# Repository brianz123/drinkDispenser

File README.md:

# Drink Dispenser

The Drink Dispenser is an Arduino-powered project designed to automatically fill one to six cups with the drink of your choice. Built as a personal engineering challenge, this project combines hardware control, PCB design, and 3D modeling to create a functional and customizable beverage distribution system.

## Summary

This project was built for fun to explore hardware control, fluid management, and embedded systems. It uses an Arduino to control a water pump and distributes fluid into up to six glasses based on user input selected with a rotary encoder. LEDs connected to an I/O expander provide visual feedback on the number of drinks selected. The mechanical frame was designed in Autodesk Inventor, and the control board was custom-designed in KiCad.

## Features

- Dispenses to 1–6 cups automatically
- Rotary encoder for selecting number of drinks
- LED display (via I/O expander) to show selection in real time
- Arduino-based pump control system
- 3D-modeled and printed parts using Autodesk Inventor
- Custom PCB designed in KiCad
- Modular design for future upgrades

## Hardware

- Arduino microcontroller
- Water pump
- Tubing and splitter manifold
- Rotary encoder
- LEDs + I/O expander (for display)
- 3D-printed frame and mounts (modeled in Inventor)
- Custom PCB (designed in KiCad)

## Software

- Arduino IDE for microcontroller programming
- Rotary encoder logic to select drink quantity
- I/O expander control for LED output
- Time-controlled activation of water pump
- Open-source and adaptable for other types of liquids or expanded glass counts

## Project Goals

- Practice PCB design using KiCad
- Integrate mechanical design with embedded electronics
- Implement real-time user input and feedback system
- Build a fully functional end-to-end automated system

## Future Improvements

- Add touchscreen interface or Bluetooth app control
- Integrate flow sensors for volume precision
- Add cleaning cycle logic for tubing
- Expand I/O expander usage for more LEDs or feedback signals

## Author

**Brian Zagalsky**

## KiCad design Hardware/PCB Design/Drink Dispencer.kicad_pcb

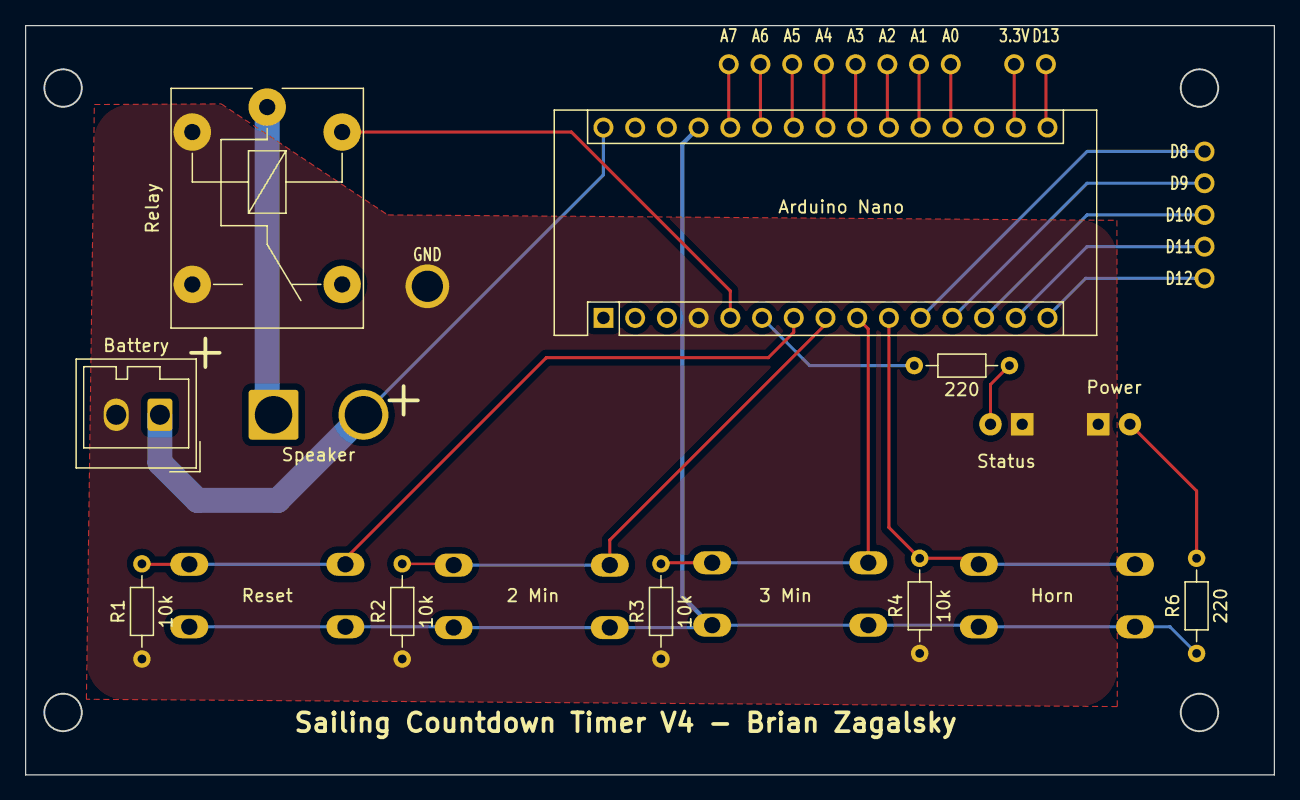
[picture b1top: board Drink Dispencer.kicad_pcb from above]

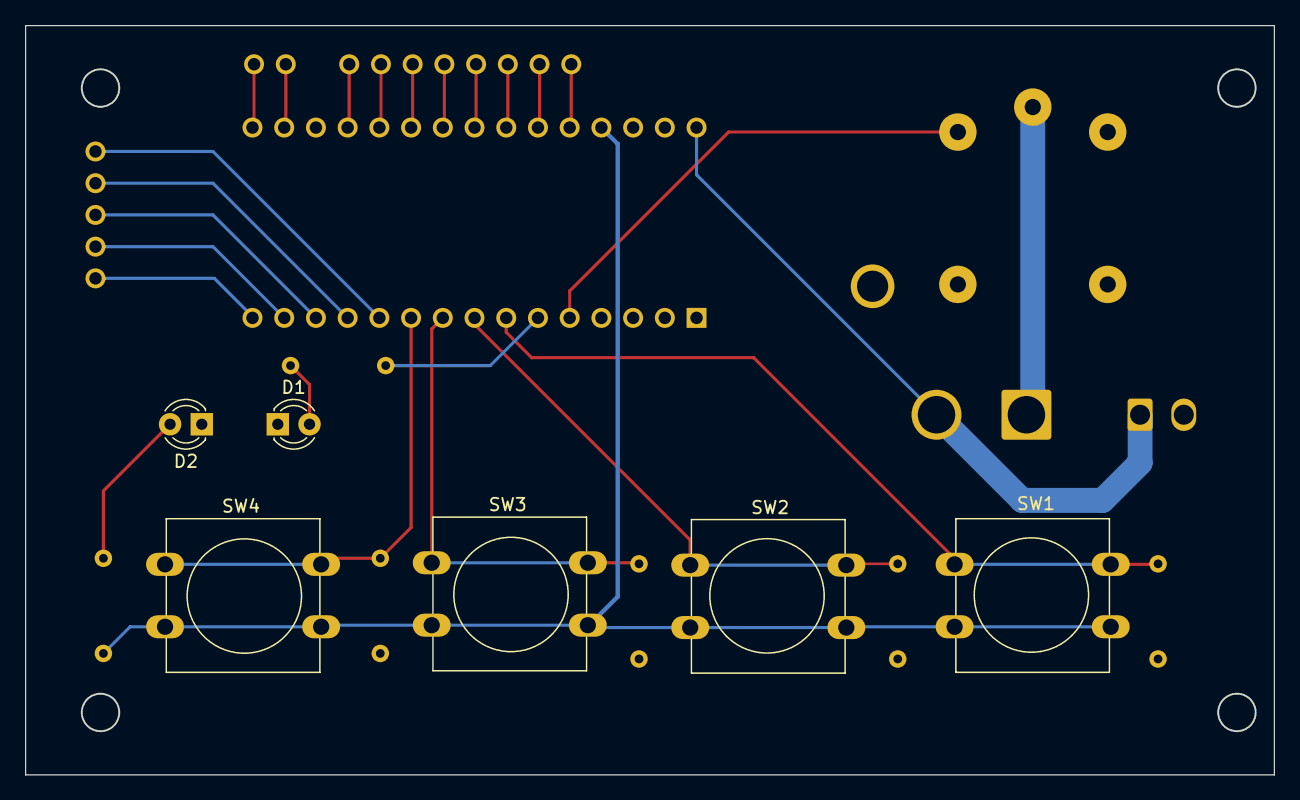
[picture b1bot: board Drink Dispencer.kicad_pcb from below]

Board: 2 copper layers, 100.0 x 59.9 mm, 32 parts (6 on the bottom side), 12 nets.

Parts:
3.3V: MountingHole_1.2mm
A0, A1, A2, A3, A4, A5, A6, A7: MountingHole_1.2mm
A1#2: Arduino Nano; Arduino_Nano
D1: Status; LED_D3.0mm
D2: Power; LED_D3.0mm
D8, D9, D10, D11, D12, D13: MountingHole_1.2mm
GND: MountingHole_1.2mm
LS1: Speaker; SolderWire-2.5sqmm_1x02_P7.2mm_D2.4mm_OD3.6mm
R1, R2, R3, R4: 10k; R_Axial_DIN0204_L3.6mm_D1.6mm_P7.62mm_Horizontal
R5, R6: 220; R_Axial_DIN0204_L3.6mm_D1.6mm_P7.62mm_Horizontal
Relay: FINDER-36.11; Relay_SPDT_Finder_36.11
SW1: Reset; SW_PUSH-12mm
SW2: 2 Min; SW_PUSH-12mm
SW3: 3 Min; SW_PUSH-12mm
SW4: Horn; SW_PUSH-12mm
V1: Battery; Wago_734-132_1x02_P3.50mm_Vertical

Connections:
/GND: A1#2.4 (GND), D1.1 (K), D2.1 (K), R1.1, R2.1, R3.1, R4.1, Relay.14, Relay.A1, V1.2 (-)
unnamed: A1#2.5 (D2), Relay.A2
unnamed: A1#2.6 (D3), R5.1
unnamed: A1#2.7 (D4), R1.2, SW1.2
unnamed: A1#2.8 (D5), R2.2, SW2.2
unnamed: A1#2.9 (D6), R3.2, SW3.1
unnamed: A1#2.10 (D7), R4.2, SW4.1
unnamed: A1#2.27 (+5V), R6.1, SW1.1, SW2.1, SW3.2, SW4.2
unnamed: A1#2.30 (VIN), LS1.2, V1.1 (+)
unnamed: D1.2 (A), R5.2
unnamed: D2.2 (A), R6.2
unnamed: LS1.1, Relay.11

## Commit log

2024-07-31 Initial Push
2025-06-30 push cad files
2025-06-30 add cad
